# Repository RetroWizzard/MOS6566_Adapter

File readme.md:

In this repo you will find all the files neccesary to order your pcb.
Please note that even though this design has been tested, there's still a risk of errors present in the design.

Whatever you do, <B>DO NOT UNDER ANY CIRCUMSTANCES close both jumbers at the same time!!!</B>
Doing so will send 12V into the 5V power cirquit of your computer and damage it.

By using this repository you agree that the author will not be held responsible for any damage to your hardware in any way.

Shield: [![CC BY-NC 4.0][cc-by-nc-shield]][cc-by-nc]

This work is licensed under a
[Creative Commons Attribution-NonCommercial 4.0 International License][cc-by-nc].

[![CC BY-NC 4.0][cc-by-nc-image]][cc-by-nc]

[cc-by-nc]: https://creativecommons.org/licenses/by-nc/4.0/
[cc-by-nc-image]: https://licensebuttons.net/l/by-nc/4.0/88x31.png
[cc-by-nc-shield]: https://img.shields.io/badge/License-CC%20BY--NC%204.0-lightgrey.svg

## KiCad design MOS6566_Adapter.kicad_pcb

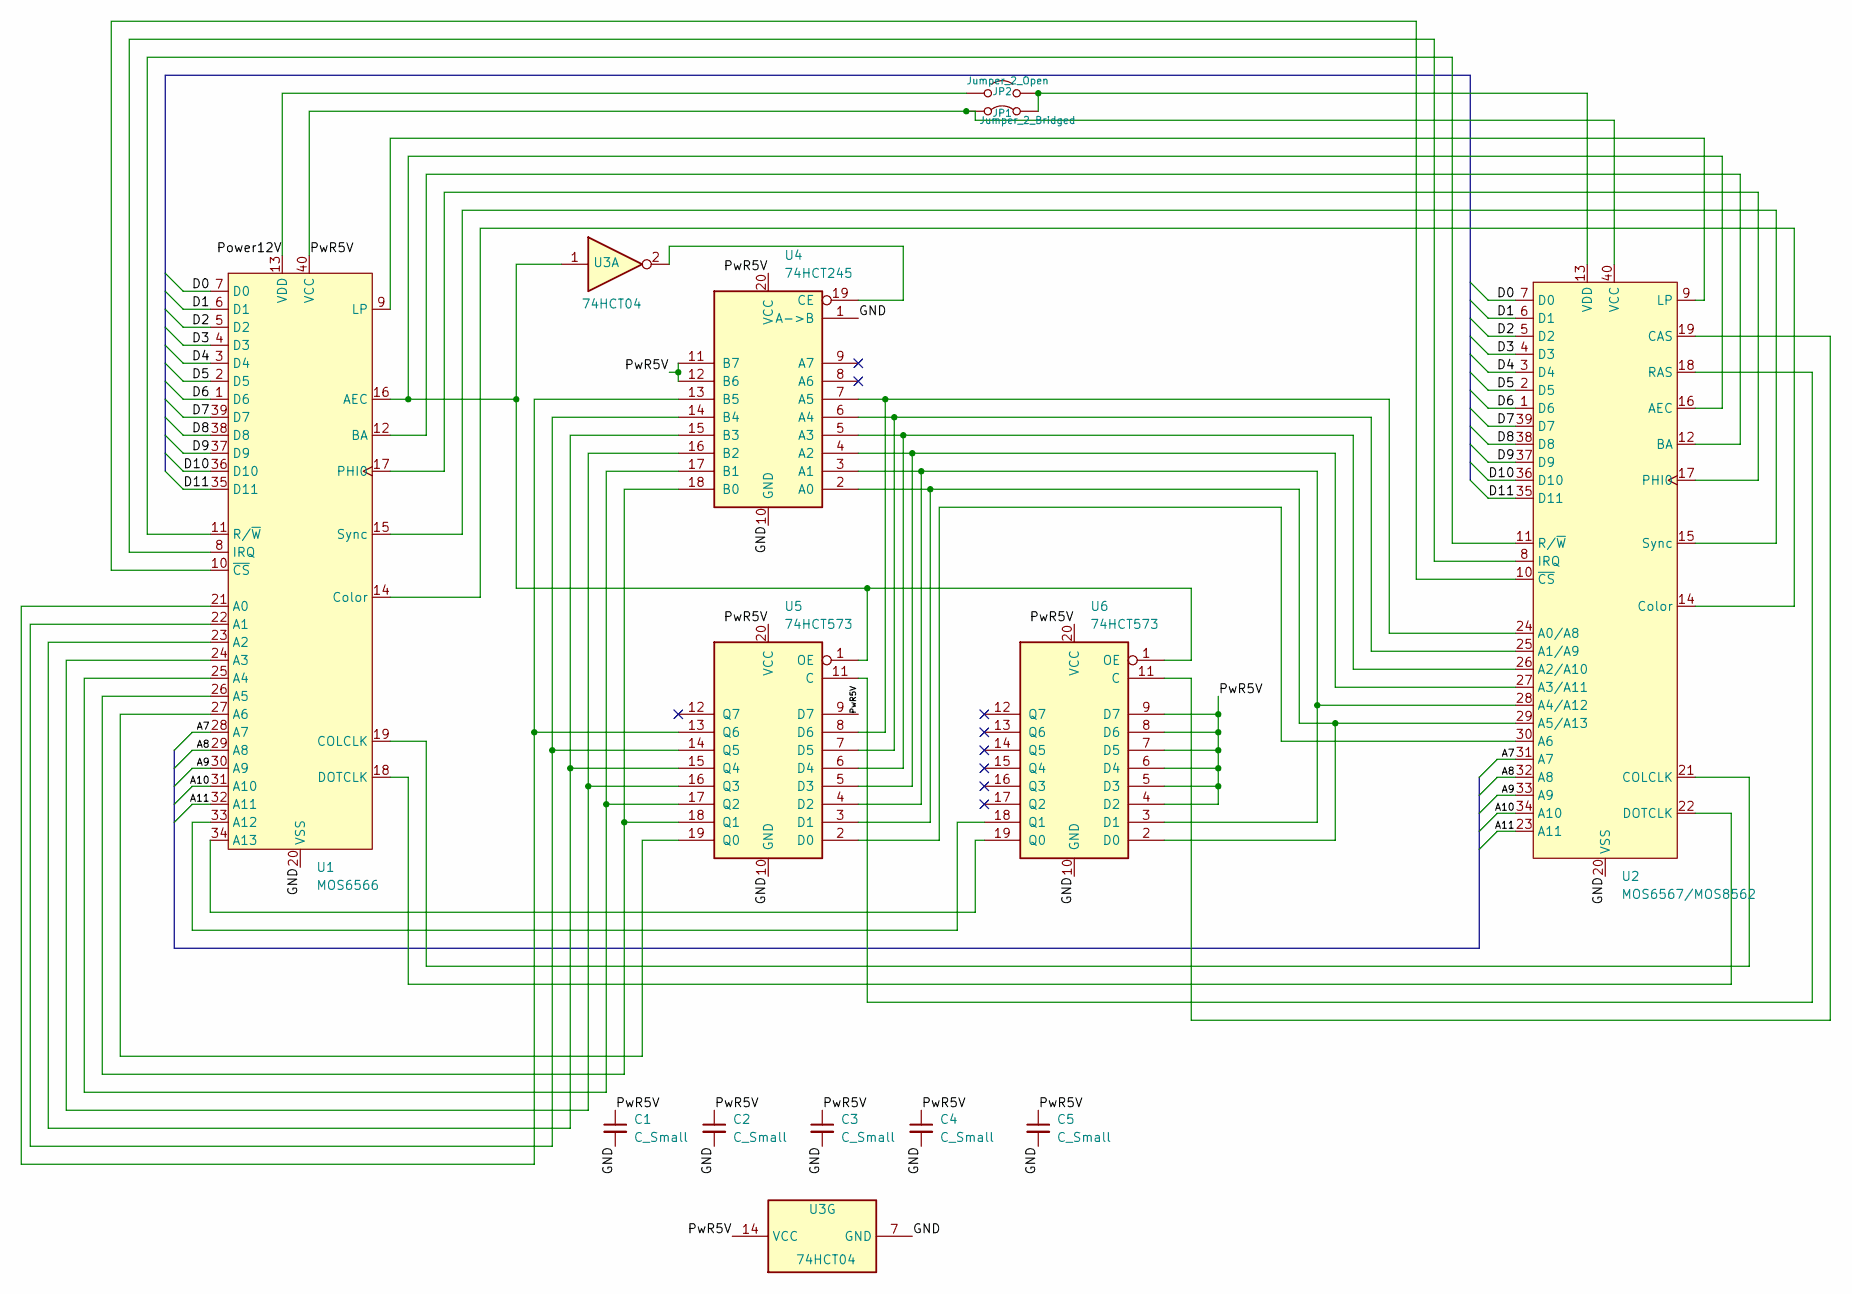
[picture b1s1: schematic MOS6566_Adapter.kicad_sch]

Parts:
C1, C2, C3, C4, C5: C_Small; C_Disc_D3.4mm_W2.1mm_P2.50mm
JP1: Jumper_2_Bridged; SolderJumper-2_P1.3mm_Bridged_RoundedPad1.0x1.5mm
JP2: Jumper_2_Open; SolderJumper-2_P1.3mm_Open_RoundedPad1.0x1.5mm
U1: MOS6566; DIP-40_W15.24mm_Socket
U2: MOS6567/MOS8562; DIP-40_W15.24mm_Socket
U3: 74HCT04; DIP-14_W7.62mm_Socket
U4: 74HCT245; DIP-20_W7.62mm_Socket
U5, U6: 74HCT573; DIP-20_W7.62mm_Socket

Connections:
/A7: U1.28 (A7), U2.31 (A7)
/A8: U1.29 (A8), U2.32 (A8)
/A9: U1.30 (A9), U2.33 (A9)
/A10: U1.31 (A10), U2.34 (A10)
/A11: U1.32 (A11), U2.23 (A11)
/D0: U1.7 (D0), U2.7 (D0)
/D1: U1.6 (D1), U2.6 (D1)
/D2: U1.5 (D2), U2.5 (D2)
/D3: U1.4 (D3), U2.4 (D3)
/D4: U1.3 (D4), U2.3 (D4)
/D5: U1.2 (D5), U2.2 (D5)
/D6: U1.1 (D6), U2.1 (D6)
/D7: U1.39 (D7), U2.39 (D7)
/D8: U1.38 (D8), U2.38 (D8)
/D9: U1.37 (D9), U2.37 (D9)
/D10: U1.36 (D10), U2.36 (D10)
/D11: U1.35 (D11), U2.35 (D11)
/GND: C1.2, C2.2, C3.2, C4.2, C5.2, U1.20 (VSS), U2.20 (VSS), U3.7 (GND), U4.1 (A->B), U4.10 (GND), U5.10 (GND), U6.10 (GND)
/Power12V: JP2.1 (A), U1.13 (VDD)
/PwR5V: C1.1, C2.1, C3.1, C4.1, C5.1, JP1.1 (A), U1.40 (VCC), U2.40 (VCC), U3.14 (VCC), U4.11 (B7), U4.12 (B6), U4.20 (VCC), U5.9 (D7), U5.20 (VCC), U6.4 (D2), U6.5 (D3), U6.6 (D4), U6.7 (D5), U6.8 (D6), U6.9 (D7), U6.20 (VCC)
unnamed: JP1.2 (B), JP2.2 (B), U2.13 (VDD)
unnamed: U1.21 (A0), U4.13 (B5), U5.13 (Q6)
unnamed: U1.22 (A1), U4.14 (B4), U5.14 (Q5)
unnamed: U1.23 (A2), U4.15 (B3), U5.15 (Q4)
unnamed: U1.24 (A3), U4.16 (B2), U5.16 (Q3)
unnamed: U1.25 (A4), U4.17 (B1), U5.17 (Q2)
unnamed: U1.26 (A5), U4.18 (B0), U5.18 (Q1)
unnamed: U1.27 (A6), U5.19 (Q0)
unnamed: U1.33 (A12), U6.18 (Q1)
unnamed: U1.34 (A13), U6.19 (Q0)
unnamed: U1.16 (AEC), U2.16 (AEC), U3.1, U5.1 (OE), U6.1 (OE)
unnamed: U1.12 (BA), U2.12 (BA)
unnamed: U1.19 (COLCLK), U2.21 (COLCLK)
unnamed: U1.14 (Color), U2.14 (Color)
unnamed: U1.18 (DOTCLK), U2.22 (DOTCLK)
unnamed: U1.8 (IRQ), U2.8 (IRQ)
unnamed: U1.9 (LP), U2.9 (LP)
unnamed: U1.17 (PHI0), U2.17 (PHI0)
unnamed: U1.11 (R/~W), U2.11 (R/~W)
unnamed: U1.15 (Sync), U2.15 (Sync)
unnamed: U1.10 (~CS), U2.10 (~CS)
unnamed: U2.24 (A0/A8), U4.7 (A5), U5.8 (D6)
unnamed: U2.25 (A1/A9), U4.6 (A4), U5.7 (D5)
unnamed: U2.26 (A2/A10), U4.5 (A3), U5.6 (D4)
unnamed: U2.27 (A3/A11), U4.4 (A2), U5.5 (D3)
unnamed: U2.28 (A4/A12), U4.3 (A1), U5.4 (D2), U6.3 (D1)
unnamed: U2.29 (A5/A13), U4.2 (A0), U5.3 (D1), U6.2 (D0)
unnamed: U2.30 (A6), U5.2 (D0)
unnamed: U2.19 (CAS), U6.11 (C)
unnamed: U2.18 (RAS), U5.11 (C)
unnamed: U3.2, U4.19 (CE)

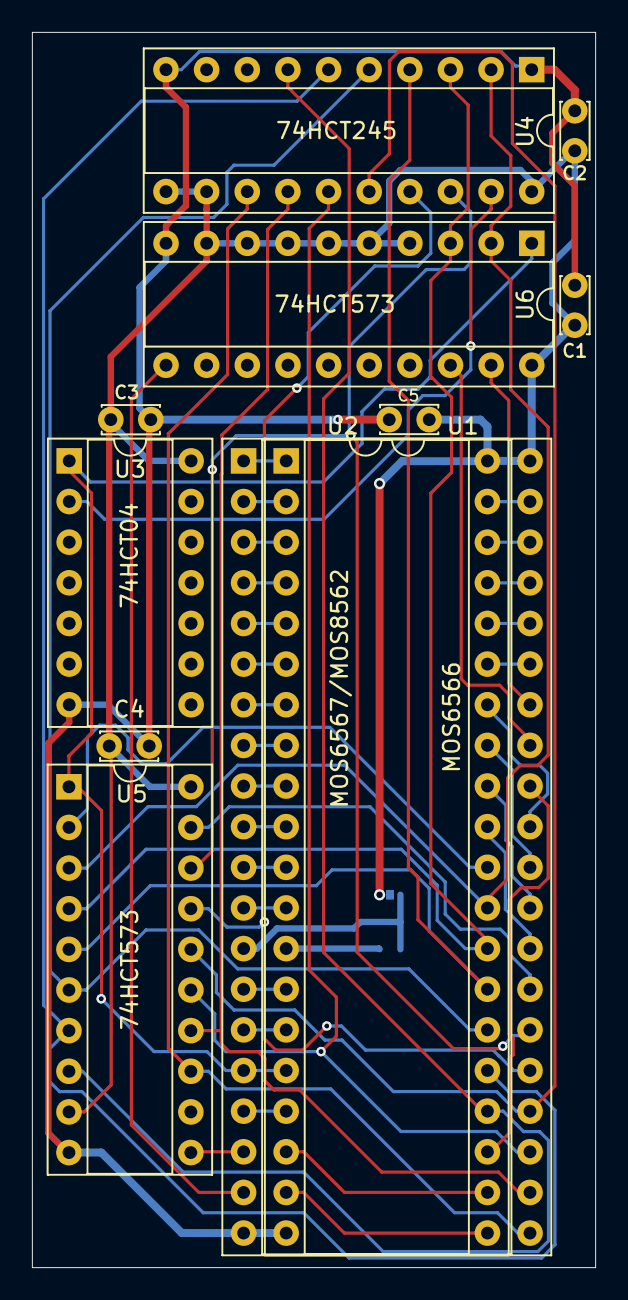
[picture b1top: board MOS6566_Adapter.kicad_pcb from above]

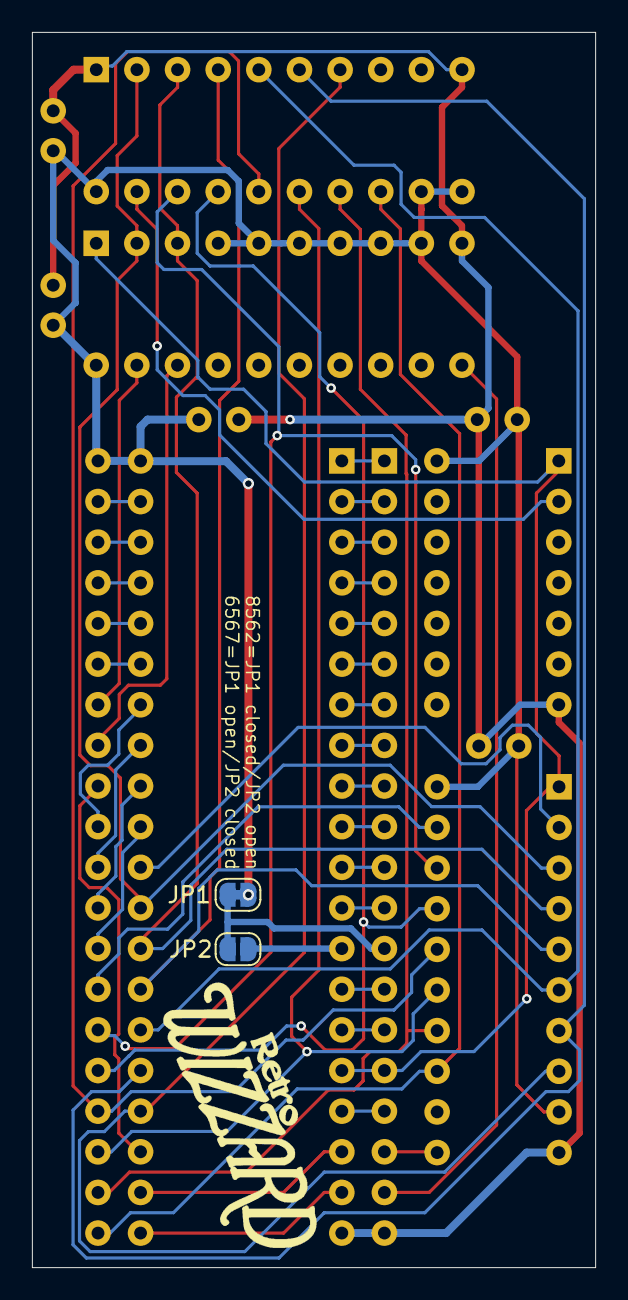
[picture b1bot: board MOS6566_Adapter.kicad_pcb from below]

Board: 2 copper layers, 35.2 x 77.2 mm, 13 parts (2 on the bottom side), 51 nets.

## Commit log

2024-05-20 Version 1.0
2024-05-20 Generated Gerber files
2024-05-20 License added
2024-06-14 Finetuning
2024-06-14 New Gerbers
2024-06-17 Minor cosmetics
2024-08-08 Cosmetics on silkscreen
2024-08-11 Updated gerbers and Readme
2024-08-11 Removed old gerbers
